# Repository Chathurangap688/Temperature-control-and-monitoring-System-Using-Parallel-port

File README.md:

# Temperature-control-and-monitoring-System-Using-Parallel-port
acadamic project CO326
## we update this to generalize realtime analog in and digital out project
  -> read 8 analog valuse and shw its in GUI via serial commiunication
  
  -> controll 8 digital out put accoding to analog input value
  
   -> this output can handael manually or automatically
   
   -> If you wont to desing hardwear, open hardwear folder, you can downlode desing file and desing the hardwear

# Please open the 'final' folder for final project 

                first run the serial.py in final folder
  This is for acces the serial port eazy
  we uuse serial to usb module for testing it's not support to java serial library. There for we use python serial library
then run main file of gui and java server in folder gui 

                Gui.java
If you cant run this without errors , you may use netbeansIDE for run it
  -> create new java project in netbeans and coppy gui folder to '.../project/src' in netbeans
  *** add 'pakege gui;' for all java files to run in netbeans

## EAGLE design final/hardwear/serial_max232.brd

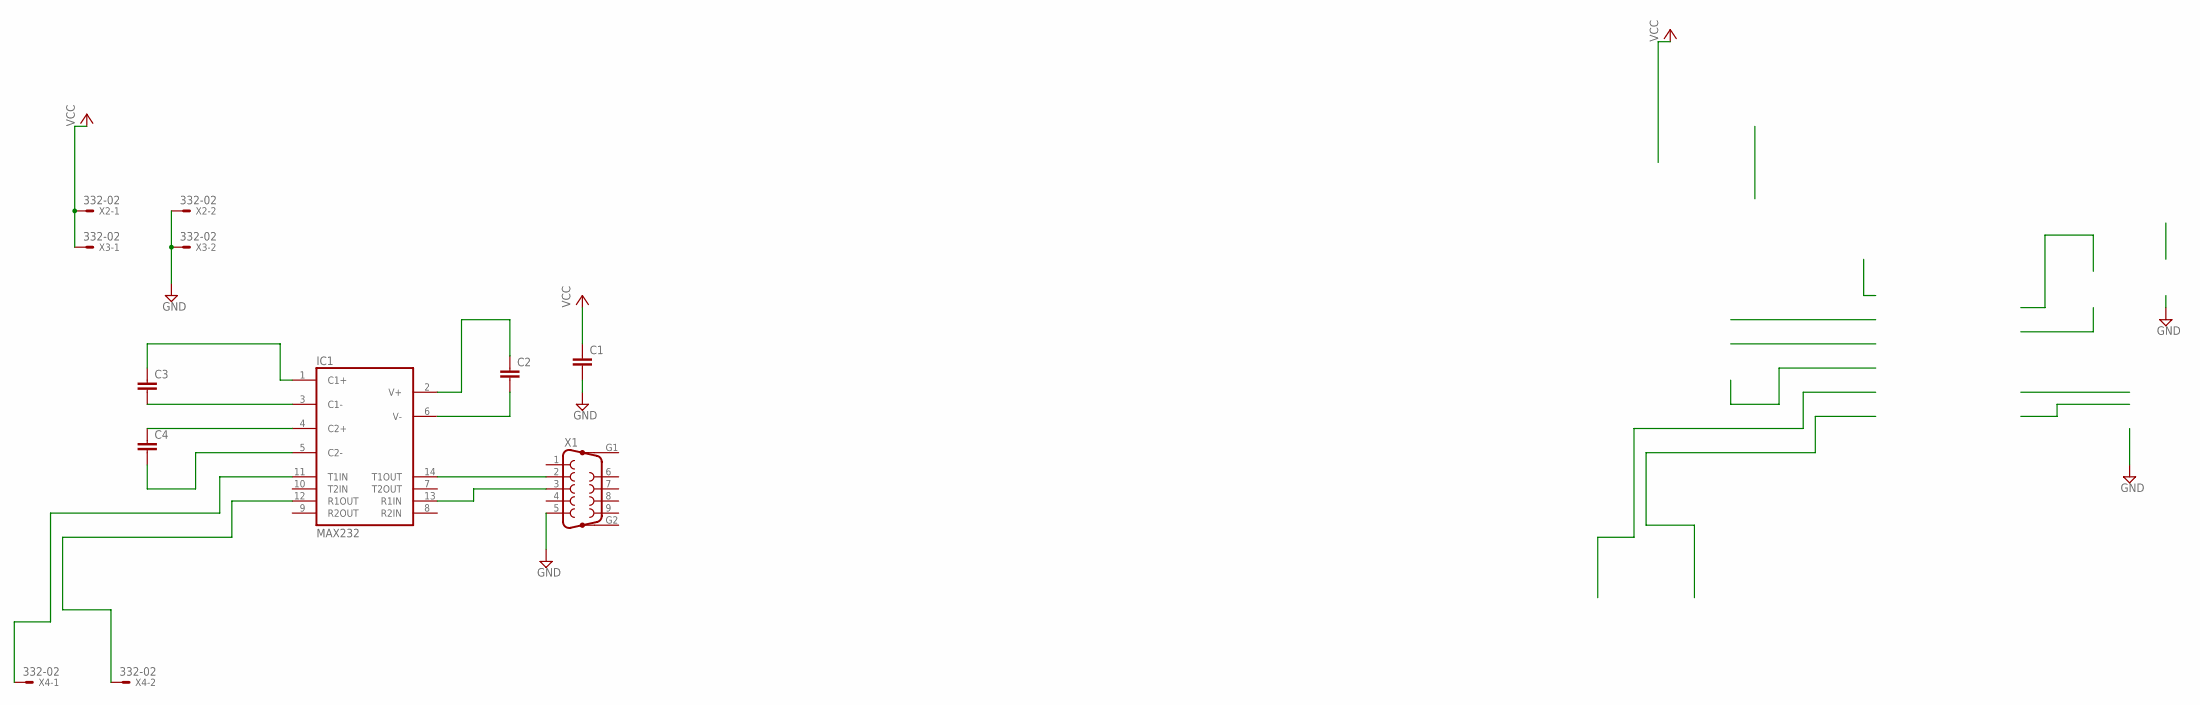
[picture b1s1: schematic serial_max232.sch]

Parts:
C1, C2, C3, C4: C5/7.2; C5B7.2
IC1: MAX232; DIL16
X1: F09VP
X2, X3, X4: 332-02

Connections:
GND: C1.2, IC1.15 (GND), X1.5, X2.2, X3.2
unnamed: IC1.14 (T1OUT), X1.2
unnamed: IC1.13 (R1IN), X1.3
unnamed: C3.1, IC1.1 (C1+)
unnamed: C2.1, IC1.2 (V+)
unnamed: C2.2, IC1.6 (V-)
unnamed: C3.2, IC1.3 (C1-)
unnamed: C4.1, IC1.4 (C2+)
unnamed: C4.2, IC1.5 (C2-)
unnamed: IC1.12 (R1OUT), X4.2
unnamed: IC1.11 (T1IN), X4.1
VCC: C1.1, IC1.16 (VCC), X2.1, X3.1

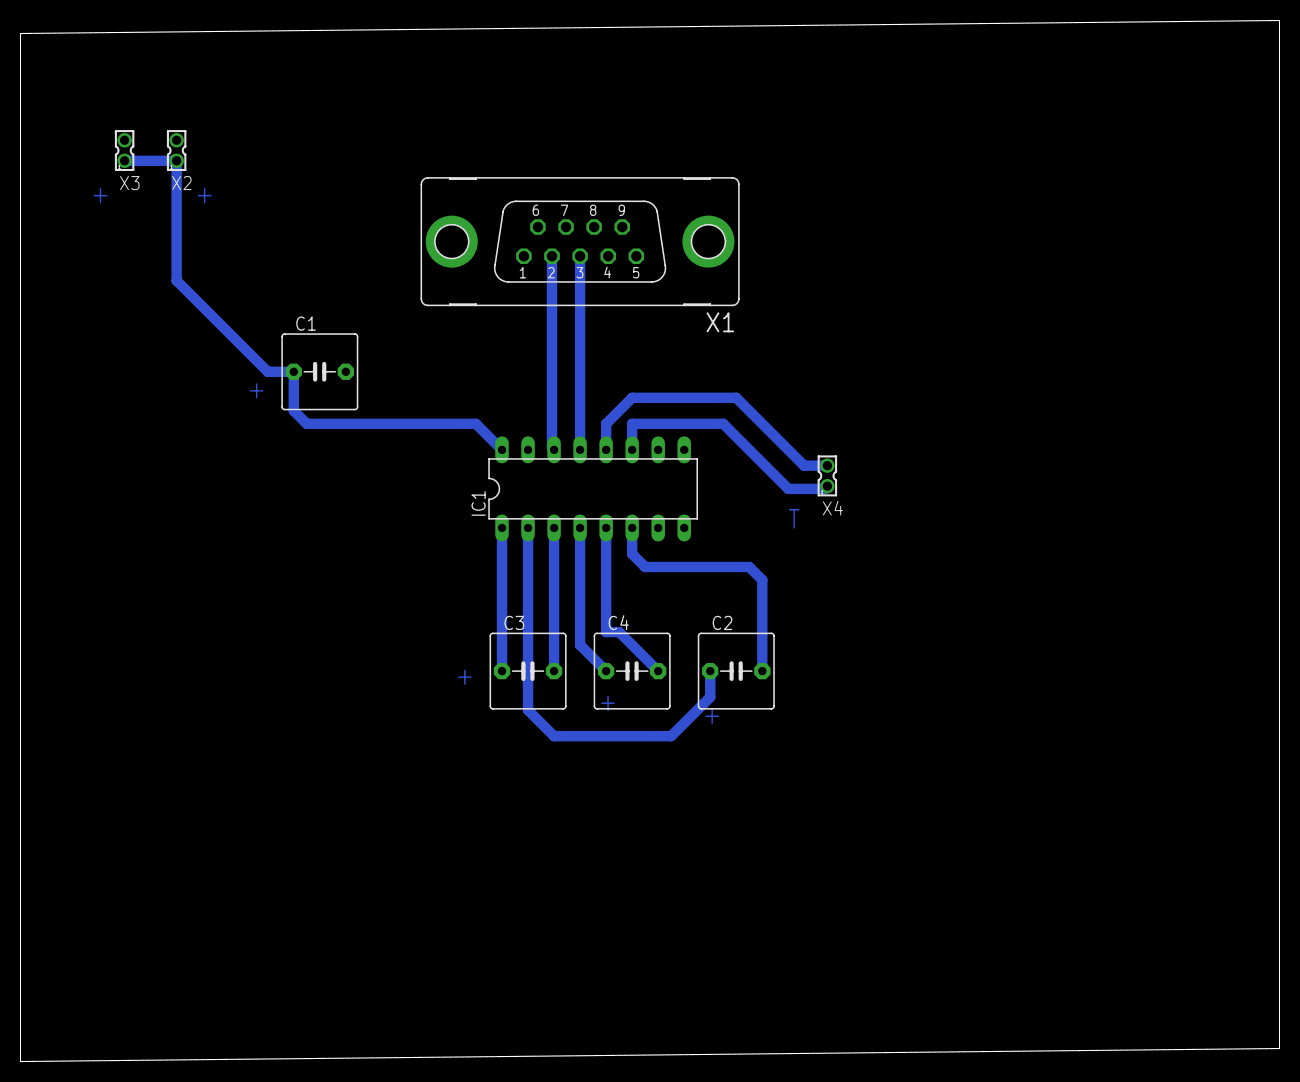
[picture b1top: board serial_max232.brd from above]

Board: 2 copper layers, 122.9 x 101.6 mm, 9 parts (0 on the bottom side), 12 nets.

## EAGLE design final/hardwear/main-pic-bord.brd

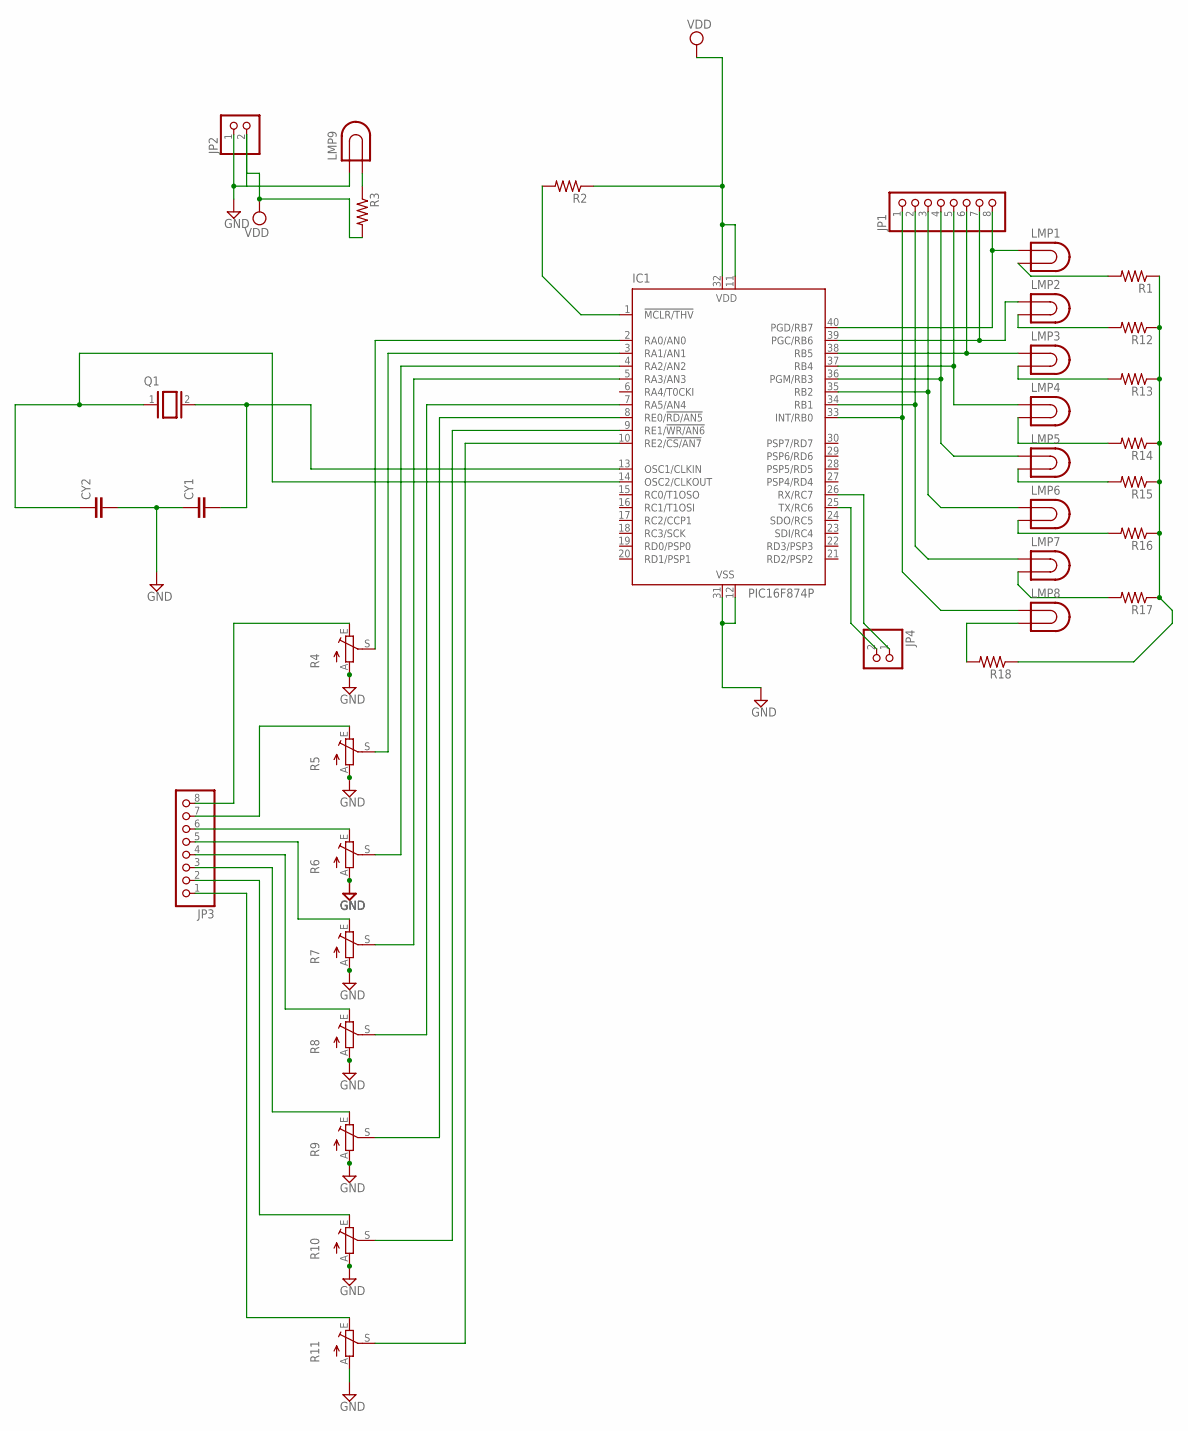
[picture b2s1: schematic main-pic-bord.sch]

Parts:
CY1, CY2: CYYC7B5; YC7B5
IC1: PIC16F874P; DIL40
JP1, JP3: PINHD-1X8; 1X08
JP2, JP4: PINHD-1X2; 1X02
LMP1, LMP2, LMP3, LMP4, LMP5, LMP6, LMP7, LMP8, LMP9: LAMP; LDH-5R
Q1: XTAL/S; QS
R1, R2, R3, R12, R13, R14, R15, R16, R17, R18: R-US_VMTB60; VMTB60
R4, R5, R6, R7, R8, R9, R10, R11: TRIM_EU-CA6V; CA6V

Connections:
GND: CY1.1, CY2.2, IC1.12 (VSS), IC1.31 (VSS), JP2.1, LMP9.1, R4.A, R5.A, R6.A, R7.A, R8.A, R9.A, R10.A, R11.A
unnamed: IC1.2 (RA0/AN0), R4.S
unnamed: IC1.3 (RA1/AN1), R5.S
unnamed: IC1.4 (RA2/AN2), R6.S
unnamed: IC1.5 (RA3/AN3), R7.S
unnamed: IC1.7 (RA5/AN4), R8.S
unnamed: IC1.8 (RE0/!RD/AN5), R9.S
unnamed: IC1.9 (RE1/!WR/AN6), R10.S
unnamed: IC1.10 (RE2/!CS/AN7), R11.S
unnamed: JP3.8, R4.E
unnamed: JP3.7, R5.E
unnamed: JP3.6, R6.E
unnamed: JP3.5, R7.E
unnamed: JP3.4, R8.E
unnamed: JP3.3, R9.E
unnamed: JP3.2, R10.E
unnamed: JP3.1, R11.E
unnamed: IC1.33 (INT/RB0), JP1.1, LMP8.1
unnamed: CY1.2, IC1.13 (OSC1/CLKIN), Q1.2
unnamed: CY2.1, IC1.14 (OSC2/CLKOUT), Q1.1
unnamed: IC1.34 (RB1), JP1.2, LMP7.1
unnamed: IC1.35 (RB2), JP1.3, LMP6.1
unnamed: IC1.36 (PGM/RB3), JP1.4, LMP5.1
unnamed: IC1.37 (RB4), JP1.5, LMP4.1
unnamed: IC1.38 (RB5), JP1.6, LMP3.1
unnamed: IC1.39 (PGC/RB6), JP1.7, LMP2.1
unnamed: IC1.40 (PGD/RB7), JP1.8, LMP1.1
unnamed: LMP9.2, R3.1
unnamed: LMP8.2, R18.2
unnamed: IC1.25 (TX/RC6), JP4.2
unnamed: IC1.26 (RX/RC7), JP4.1
unnamed: LMP7.2, R17.2
unnamed: LMP6.2, R16.2
unnamed: LMP2.2, R12.2
unnamed: IC1.1 (!MCLR/THV), R2.2
unnamed: LMP5.2, R15.2
unnamed: LMP4.2, R14.2
unnamed: LMP3.2, R13.2
unnamed: LMP1.2, R1.2
unnamed: R1.1, R12.1, R13.1, R14.1, R15.1, R16.1, R17.1, R18.1
VDD: IC1.11 (VDD), IC1.32 (VDD), JP2.2, R2.1, R3.2

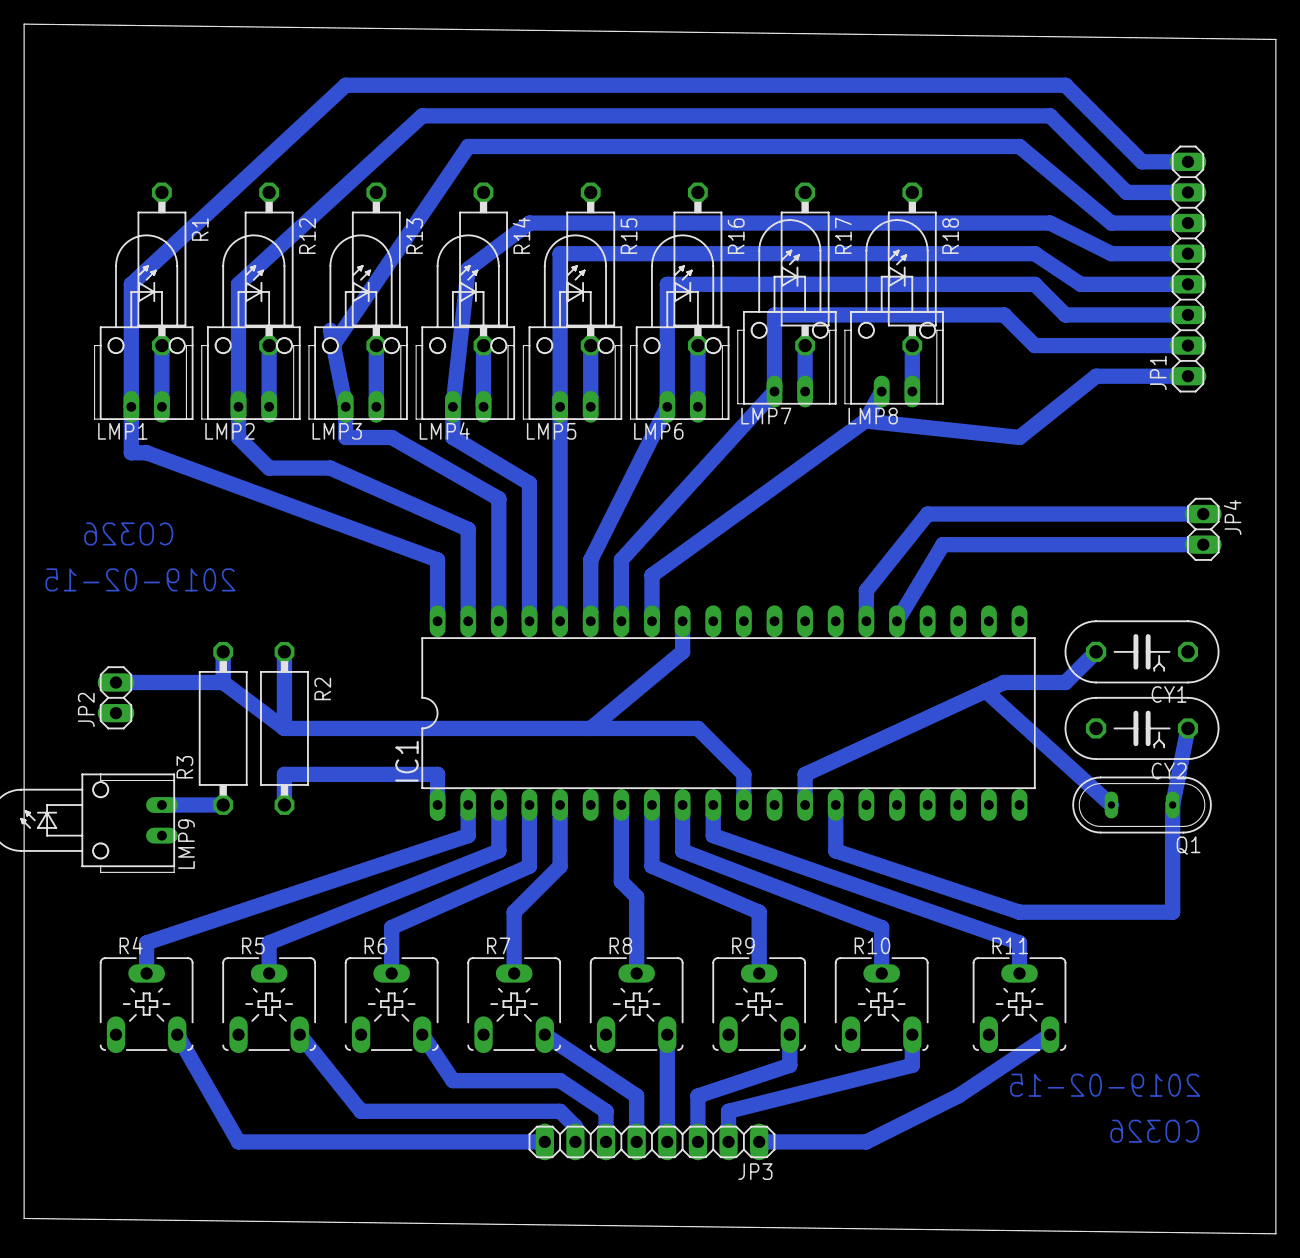
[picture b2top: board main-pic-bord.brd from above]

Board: 2 copper layers, 103.8 x 100.3 mm, 35 parts (0 on the bottom side), 41 nets.

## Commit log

2019-01-17 serialReader.c
2019-01-17 Rename serailReader to serailReader.c
2019-01-21 Rename serailReader.c to serialReader.c
2019-02-23 java Gui
2019-02-23 update new project
2019-02-23 serrial communication with python
2019-02-23 Rename serila.py to serial.py
2019-02-23 updated project
2019-02-23 Rename seriala.py to serila.py
2019-02-23 pic code
2019-02-23 hardwear file egal sft
2019-10-31 state change
2019-10-31 change auther
